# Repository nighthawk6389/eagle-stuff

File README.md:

# eagle-stuff
Stuff I made for PCB in Eagle

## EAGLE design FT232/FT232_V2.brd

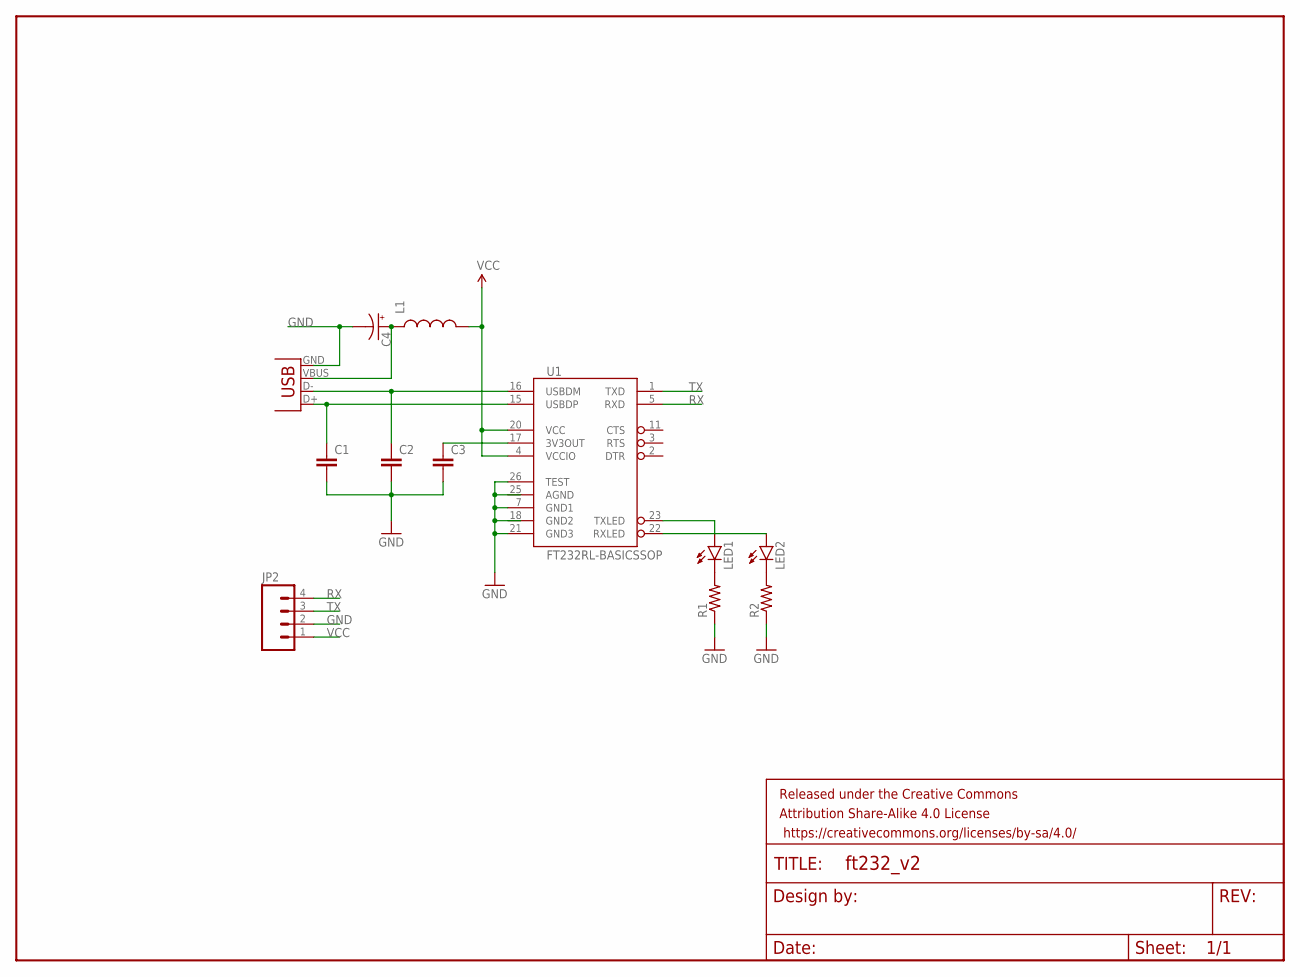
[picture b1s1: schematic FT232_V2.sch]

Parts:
C1, C2, C3: CAP0603-CAP; 0603-CAP
C4: CAP_POL1206; EIA3216
FRAME1: FRAME-LETTER; CREATIVE_COMMONS
JP1: USB-B; USB-B-PTH
JP2: M04PTH; 1X04
L1: INDUCTOR0603; 0603
LED1, LED2: LED0603; LED-0603
R1, R2: RESISTOR0603; 0603-RES
U1: FT232RL-BASICSSOP; SSOP28DB

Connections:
AGND: U1.25 (AGND)
GND: C1.2, C2.2, C3.2, C4.C (-), JP1.GND, JP2.2, R1.1, R2.1, U1.7 (GND1), U1.21 (GND3), U1.26 (TEST)
GND2: U1.18 (GND2)
unnamed: C2.1, JP1.D-, U1.16 (USBDM)
unnamed: C3.1, U1.17 (3V3OUT)
unnamed: C4.A (+), JP1.VBUS, L1.1
unnamed: C1.1, JP1.D+, U1.15 (USBDP)
unnamed: LED1.C, R1.2
unnamed: LED2.C, R2.2
unnamed: LED1.A, U1.23 (TXLED)
unnamed: LED2.A, U1.22 (RXLED)
RX: JP2.4, U1.5 (RXD)
TX: JP2.3, U1.1 (TXD)
VCC: JP2.1, L1.2, U1.4 (VCCIO), U1.20 (VCC)

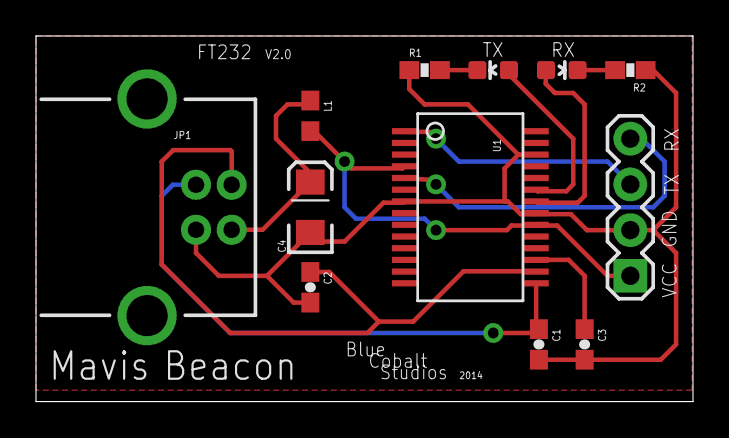
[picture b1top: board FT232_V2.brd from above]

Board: 2 copper layers, 36.5 x 20.3 mm, 13 parts (0 on the bottom side), 12 nets.

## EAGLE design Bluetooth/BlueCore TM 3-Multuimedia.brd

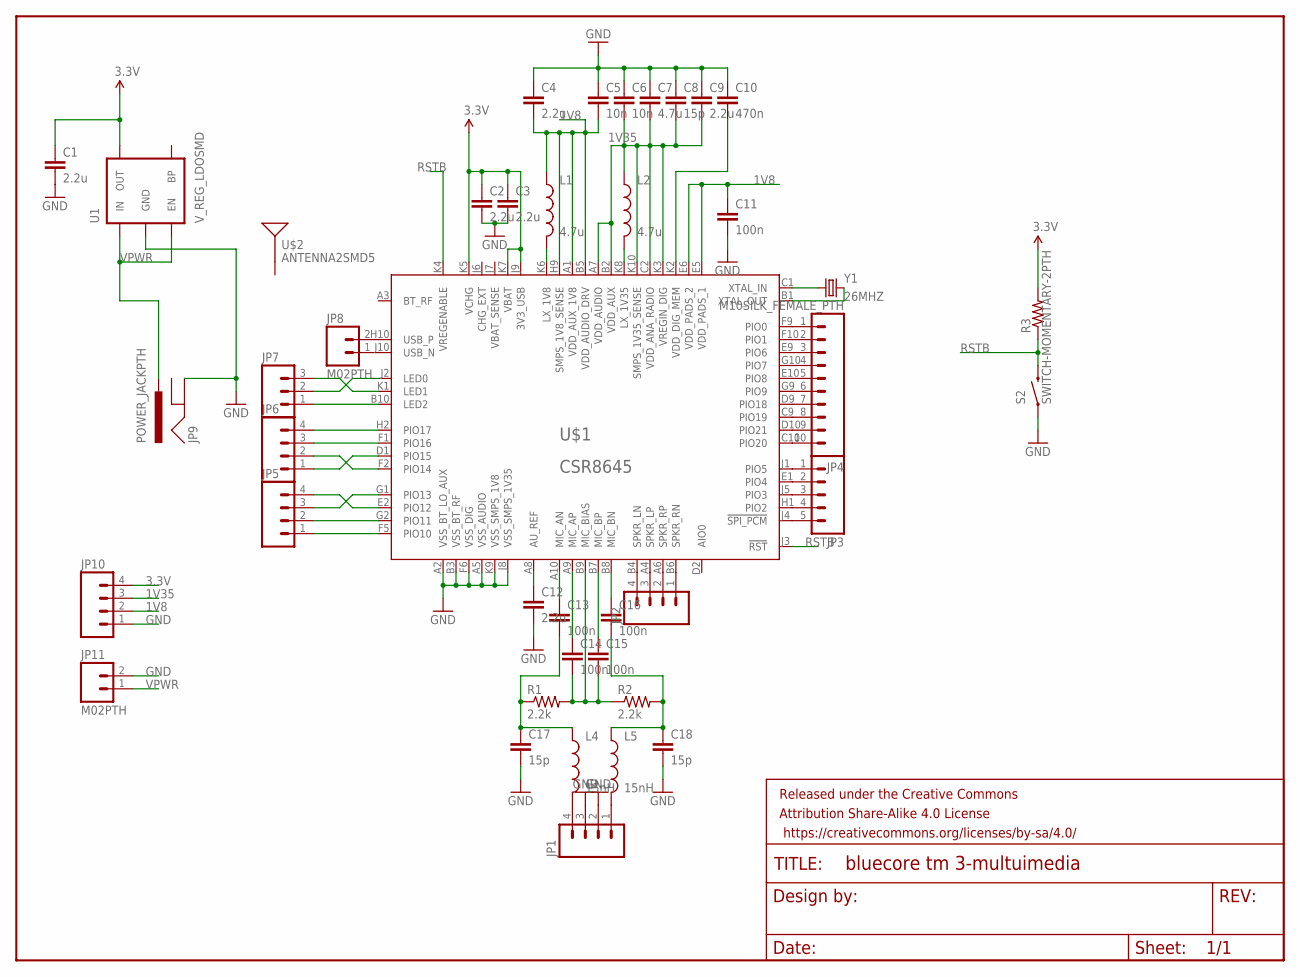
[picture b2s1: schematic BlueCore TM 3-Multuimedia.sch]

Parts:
C1, C2, C3, C4, C9, C12: 2.2u; CAP-PTH-SMALL
C5, C6: 10n; CAP-PTH-SMALL
C7: 4.7u; CAP-PTH-SMALL
C8, C17, C18: 15p; CAP-PTH-SMALL
C10: 470n; CAP-PTH-SMALL
C11, C13, C14, C15, C16: 100n; CAP-PTH-SMALL
FRAME1: FRAME-LETTER; CREATIVE_COMMONS
JP1, JP2, JP5, JP6, JP10: M04PTH; 1X04
JP3: M05PTH; 1X05
JP4: M10SILK_FEMALE_PTH; 1X10
JP7: M03PTH; 1X03
JP8, JP11: M02PTH; 1X02
JP9: POWER_JACKPTH; POWER_JACK_PTH
L1, L2: 4.7u; 0805
L4, L5: 15nH; 0805
R1, R2: 2.2k; 0805
R3: RESISTOR0805-RES; 0805
S2: SWITCH-MOMENTARY-2PTH; TACTILE-PTH
U1: V_REG_LDOSMD; SOT23-5
U$1: CSR8645; VFBGA68
U$2: ANTENNA2SMD5; ANTENNA-CHIP5
Y1: 26MHZ; HC49US

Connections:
1V8: C4.2, C5.2, C11.1, JP10.2, L1.1, U$1.A1 (VDD_AUX_1V8), U$1.B5 (VDD_AUDIO_DRV), U$1.E5 (VDD_PADS_1), U$1.E6 (VDD_PADS_2), U$1.H9 (SMPS_1V8_SENSE)
1V35: C6.2, C7.2, C8.2, C9.2, JP10.3, L2.1, U$1.A7 (VDD_AUDIO), U$1.B2 (VDD_AUX), U$1.C2 (VDD_ANA_RADIO), U$1.K3 (VREGIN_DIG), U$1.K10 (SMPS_1V35_SENSE)
3.3V: C1.1, C2.1, C3.1, JP10.4, R3.2, U1.5 (OUT), U$1.J9 (3V3_USB), U$1.K5 (VCHG), U$1.K7 (VBAT)
GND: C1.2, C2.2, C3.2, C4.1, C5.1, C6.1, C7.1, C8.1, C9.1, C10.1, C11.2, C12.2, C17.2, C18.2, JP1.2, JP1.3, JP9.GND, JP10.1, JP11.2, S2.1, U1.2 (GND), U$1.A2 (VSS_BT_LO_AUX), U$1.A5 (VSS_AUDIO), U$1.B3 (VSS_BT_RF), U$1.F6 (VSS_DIG), U$1.J8 (VSS_SMPS_1V35), U$1.K9 (VSS_SMPS_1V8)
unnamed: JP1.4, L4.2
unnamed: JP4.1, U$1.F9 (PIO0)
unnamed: L1.2, U$1.K6 (LX_1V8)
unnamed: L2.2, U$1.K8 (LX_1V35)
unnamed: U$1.C1 (XTAL_IN), Y1.1
unnamed: C10.2, U$1.K2 (VDD_DIG_MEM)
unnamed: U$1.B1 (XTAL_OUT), Y1.2
unnamed: C12.1, U$1.A8 (AU_REF)
unnamed: JP1.1, L5.2
unnamed: JP2.1, U$1.B6 (SPKR_RN)
unnamed: C13.2, C17.1, L4.1, R1.1
unnamed: JP2.2, U$1.A6 (SPKR_RP)
unnamed: C14.2, C15.2, R1.2, R2.1, U$1.B9 (MIC_BIAS)
unnamed: C13.1, U$1.A10 (MIC_AN)
unnamed: C14.1, U$1.A9 (MIC_AP)
unnamed: C15.1, U$1.B7 (MIC_BP)
unnamed: C16.1, U$1.B8 (MIC_BN)
unnamed: C16.2, C18.1, L5.1, R2.2
unnamed: JP2.3, U$1.A4 (SPKR_LP)
unnamed: JP2.4, U$1.B4 (SPKR_LN)
unnamed: JP4.2, U$1.F10 (PIO1)
unnamed: JP4.3, U$1.E9 (PIO6)
unnamed: JP4.4, U$1.G10 (PIO7)
unnamed: JP4.5, U$1.E10 (PIO8)
unnamed: JP4.6, U$1.G9 (PIO9)
unnamed: JP4.7, U$1.D9 (PIO18)
unnamed: JP4.8, U$1.C9 (PIO19)
unnamed: JP4.9, U$1.D10 (PIO21)
unnamed: JP4.10, U$1.C10 (PIO20)
unnamed: JP3.1, U$1.J1 (PIO5)
unnamed: JP3.2, U$1.E1 (PIO4)
unnamed: JP3.3, U$1.J5 (PIO3)
unnamed: JP3.4, U$1.H1 (PIO2)
unnamed: JP3.5, U$1.J4 (!SPI_PCM)
unnamed: JP5.1, U$1.F5 (PIO10)
unnamed: JP5.2, U$1.G2 (PIO11)
unnamed: JP5.4, U$1.E2 (PIO12)
unnamed: JP5.3, U$1.G1 (PIO13)
unnamed: JP6.1, U$1.D1 (PIO15)
unnamed: JP6.2, U$1.F2 (PIO14)
unnamed: JP6.3, U$1.F1 (PIO16)
unnamed: JP6.4, U$1.H2 (PIO17)
unnamed: JP7.1, U$1.B10 (LED2)
unnamed: JP7.3, U$1.K1 (LED1)
unnamed: JP7.2, U$1.J2 (LED0)
unnamed: JP8.1, U$1.J10 (USB_N)
unnamed: JP8.2, U$1.H10 (USB_P)
RSTB: R3.1, S2.3 (2), U$1.J3 (!RST), U$1.K4 (VREGENABLE)
VPWR: JP9.PWR, JP11.1, U1.1 (IN), U1.3 (EN)

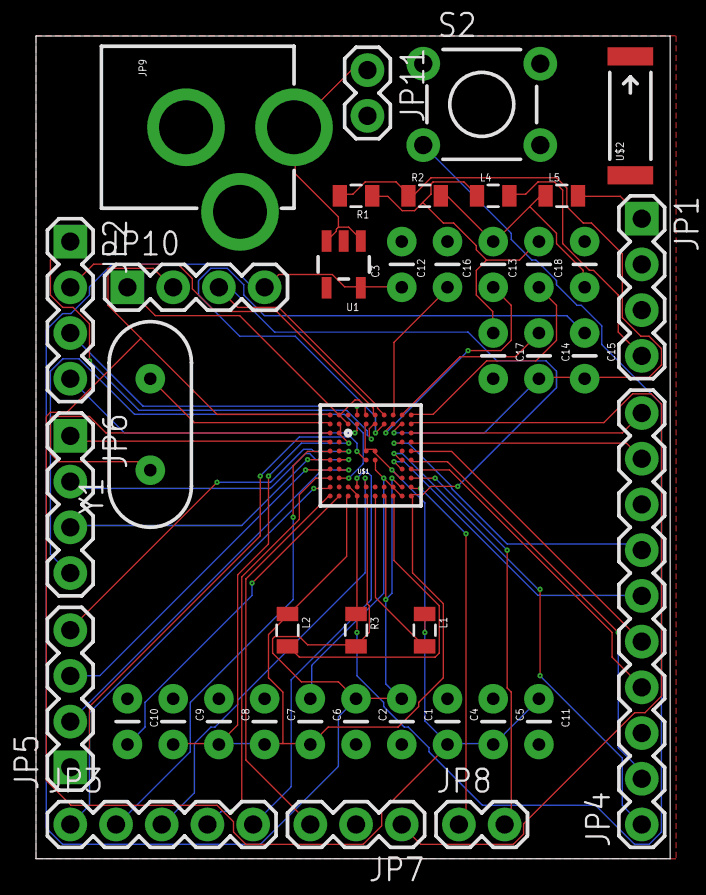
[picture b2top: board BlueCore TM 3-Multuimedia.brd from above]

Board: 2 copper layers, 35.2 x 45.7 mm, 42 parts (0 on the bottom side), 53 nets.

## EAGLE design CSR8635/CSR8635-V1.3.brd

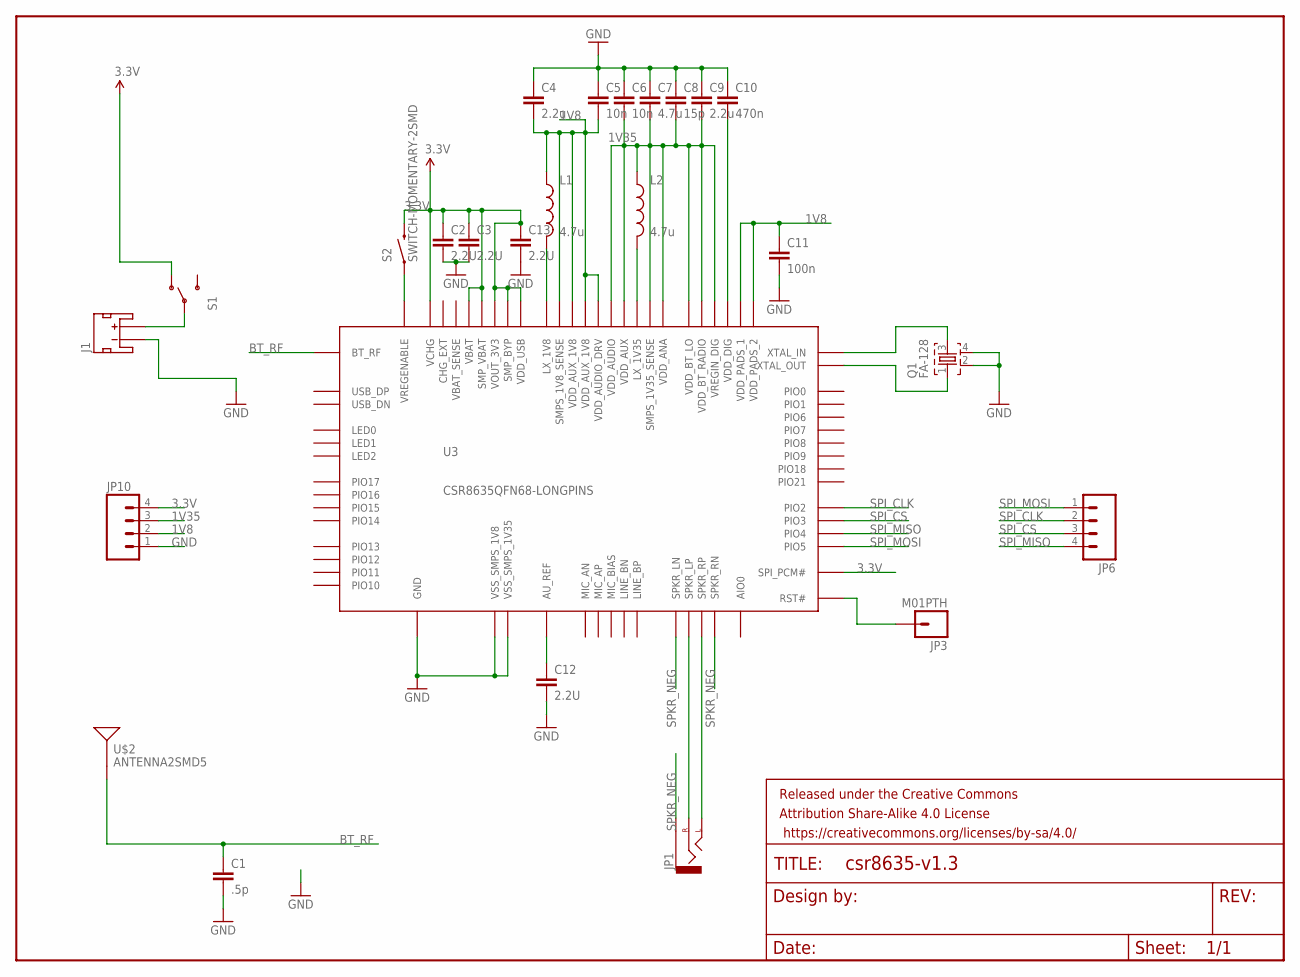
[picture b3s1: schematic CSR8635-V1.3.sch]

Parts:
C1: .5p; 0603-CAP
C2, C3, C12, C13: 2.2U; 0603-CAP
C4, C9: 2.2u; 0603-CAP
C5, C6: 10n; 0603-CAP
C7: 4.7u; 0603-CAP
C8: 15p; 0603-CAP
C10: 470n; 0603-CAP
C11: 100n; 0603-CAP
FRAME1: FRAME-LETTER; CREATIVE_COMMONS
J1: JST_2MM_MALE; JST-2-SMD
JP1: AUDIO-JACKSMD2; AUDIO-JACK-3.5MM-SMD
JP3: M01PTH; 1X01
JP6, JP10: M04PTH; 1X04
L1, L2: 4.7u; 0805
Q1: FA-128
S1: SWITCH-SPDTPTH; SWITCH-SPDT
S2: SWITCH-MOMENTARY-2SMD; TACTILE-SWITCH-SMD
U3: CSR8635QFN68-LONGPINS; QFN68
U$2: ANTENNA2SMD5; ANTENNA-CHIP5

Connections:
1V8: C4.2, C5.2, C11.1, JP10.2, L1.1, U3.8 (VDD_AUDIO_DRV), U3.15 (VDD_AUX_1V8), U3.16 (VDD_AUX_1V8), U3.33 (VDD_PADS_1), U3.53 (SMPS_1V8_SENSE), U3.63 (VDD_PADS_2)
1V35: C6.2, C7.2, C8.2, C9.2, JP10.3, L2.1, U3.3 (VDD_AUDIO), U3.11 (VDD_BT_RADIO), U3.13 (VDD_BT_LO), U3.14 (VDD_AUX), U3.17 (VDD_ANA), U3.39 (VREGIN_DIG), U3.52 (SMPS_1V35_SENSE)
3.3V: C2.1, C3.1, C13.1, JP10.4, S1.1 (O), S2.3 (2), U3.29 (SPI_PCM#), U3.41 (VOUT_3V3), U3.42 (VCHG), U3.45 (VBAT), U3.48 (SMP_VBAT), U3.49 (SMP_BYP), U3.54 (VDD_USB)
!SPI_PCM: JP3.1, U3.35 (RST#)
BT_RF: C1.1, U3.12 (BT_RF), U$2.FEED
GND: C1.2, C2.2, C3.2, C4.1, C5.1, C6.1, C7.1, C8.1, C9.1, C10.1, C11.2, C12.2, C13.2, J1.1 (-), JP10.1, Q1.2, Q1.4, U3.46 (VSS_SMPS_1V8), U3.51 (VSS_SMPS_1V35), U3.CNTR (GND), U3.CNTR1 (GND), U3.CNTR2 (GND), U3.CNTR3 (GND)
unnamed: J1.2 (+), S1.2
unnamed: JP1.RING (RIGHT), U3.10 (SPKR_LP)
unnamed: L1.2, U3.47 (LX_1V8)
unnamed: Q1.3, U3.19 (XTAL_IN)
unnamed: L2.2, U3.50 (LX_1V35)
unnamed: C10.2, U3.38 (VDD_DIG)
unnamed: Q1.1, U3.18 (XTAL_OUT)
unnamed: JP1.TIP (LEFT), U3.7 (SPKR_RP)
unnamed: C12.1, U3.1 (AU_REF)
unnamed: S2.1, U3.40 (VREGENABLE)
SPI_CLK: JP6.2, U3.30 (PIO2)
SPI_CS: JP6.3, U3.28 (PIO3)
SPI_MISO: JP6.4, U3.24 (PIO4)
SPI_MOSI: JP6.1, U3.34 (PIO5)
SPKR_NEG: JP1.SLEEVE, U3.6 (SPKR_RN), U3.9 (SPKR_LN)

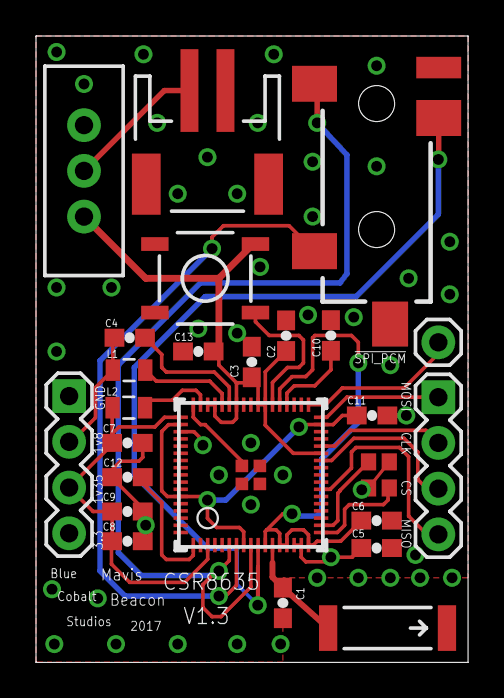
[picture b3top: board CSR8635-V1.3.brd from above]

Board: 4 copper layers, 24.0 x 34.8 mm, 26 parts (0 on the bottom side), 21 nets.

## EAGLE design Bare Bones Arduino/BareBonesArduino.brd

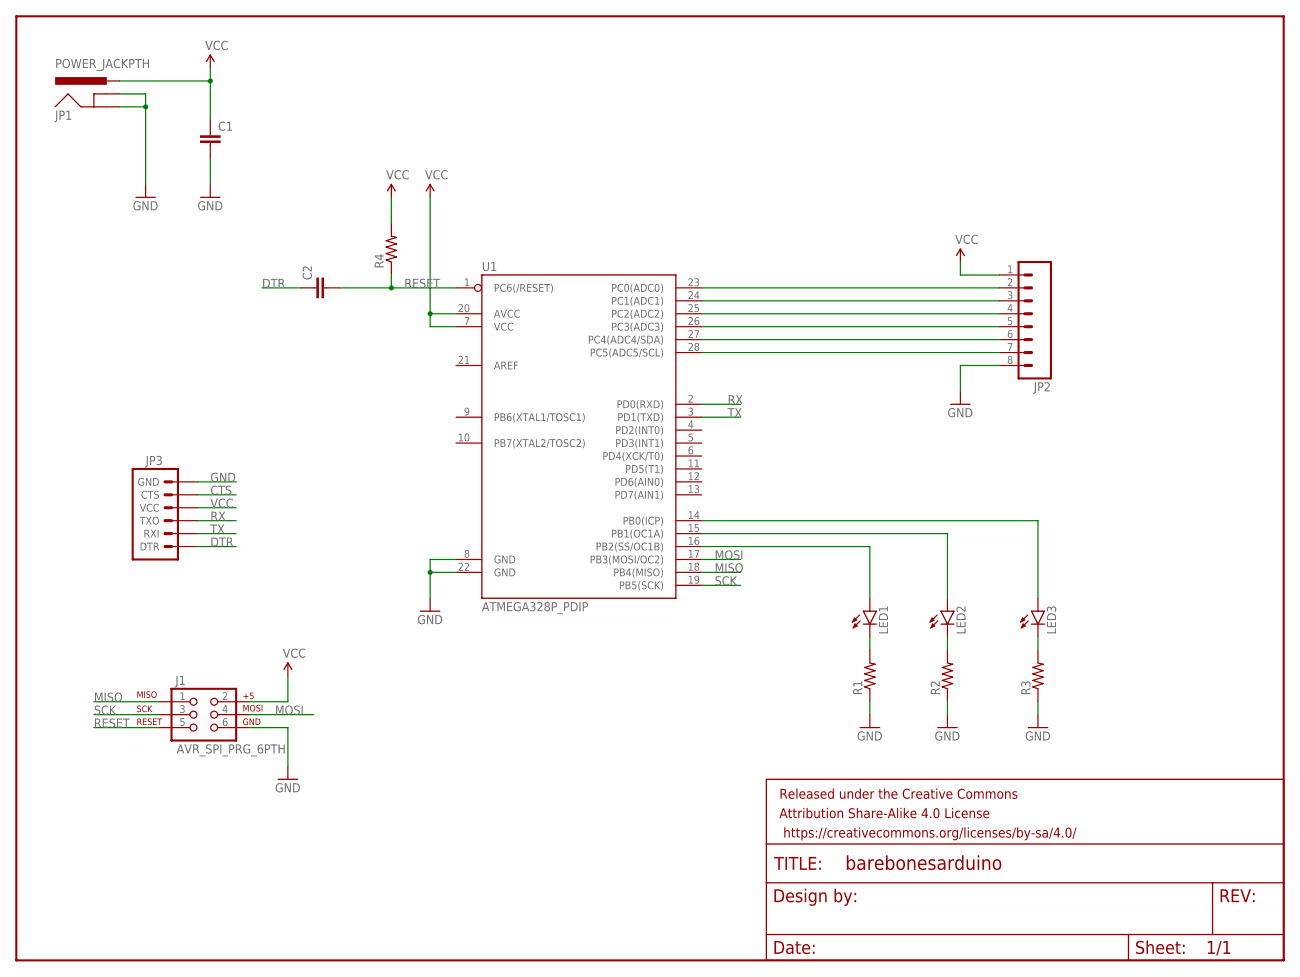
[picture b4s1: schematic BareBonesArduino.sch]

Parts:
C1, C2: CAPPTH; CAP-PTH-SMALL
FRAME1: FRAME-LETTER; CREATIVE_COMMONS
J1: AVR_SPI_PRG_6PTH; 2X3
JP1: POWER_JACKPTH; POWER_JACK_PTH
JP2: M08; 1X08_ROUND
JP3: ARDUINO_SERIAL_PROGRAMPTH; 1X06
LED1, LED2, LED3: LED5MM
R1, R2, R3, R4: RESISTORPTH-1/4W; AXIAL-0.4
U1: ATMEGA328P_PDIP; DIL28-3

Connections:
CTS: JP3.5 (CTS)
DTR: C2.1, JP3.1 (DTR)
GND: C1.2, J1.6, JP1.GND, JP1.GNDBREAK, JP2.8, JP3.6 (GND), R1.P$1 (1), R2.P$1 (1), R3.P$1 (1), U1.8 (GND), U1.22 (GND)
MISO: J1.1, U1.18 (PB4(MISO))
MOSI: J1.4, U1.17 (PB3(MOSI/OC2))
unnamed: LED3.K (C), R3.P$2 (2)
unnamed: LED2.K (C), R2.P$2 (2)
unnamed: LED1.K (C), R1.P$2 (2)
unnamed: LED1.A, U1.16 (PB2(SS/OC1B))
unnamed: LED2.A, U1.15 (PB1(OC1A))
unnamed: LED3.A, U1.14 (PB0(ICP))
unnamed: JP2.7, U1.28 (PC5(ADC5/SCL))
unnamed: JP2.6, U1.27 (PC4(ADC4/SDA))
unnamed: JP2.5, U1.26 (PC3(ADC3))
unnamed: JP2.4, U1.25 (PC2(ADC2))
unnamed: JP2.3, U1.24 (PC1(ADC1))
unnamed: JP2.2, U1.23 (PC0(ADC0))
RESET: C2.2, J1.5, R4.P$1 (1), U1.1 (PC6(/RESET))
RX: JP3.3 (TXO), U1.2 (PD0(RXD))
SCK: J1.3, U1.19 (PB5(SCK))
TX: JP3.2 (RXI), U1.3 (PD1(TXD))
VCC: C1.1, J1.2, JP1.PWR, JP2.1, JP3.4 (VCC), R4.P$2 (2), U1.7 (VCC), U1.20 (AVCC)

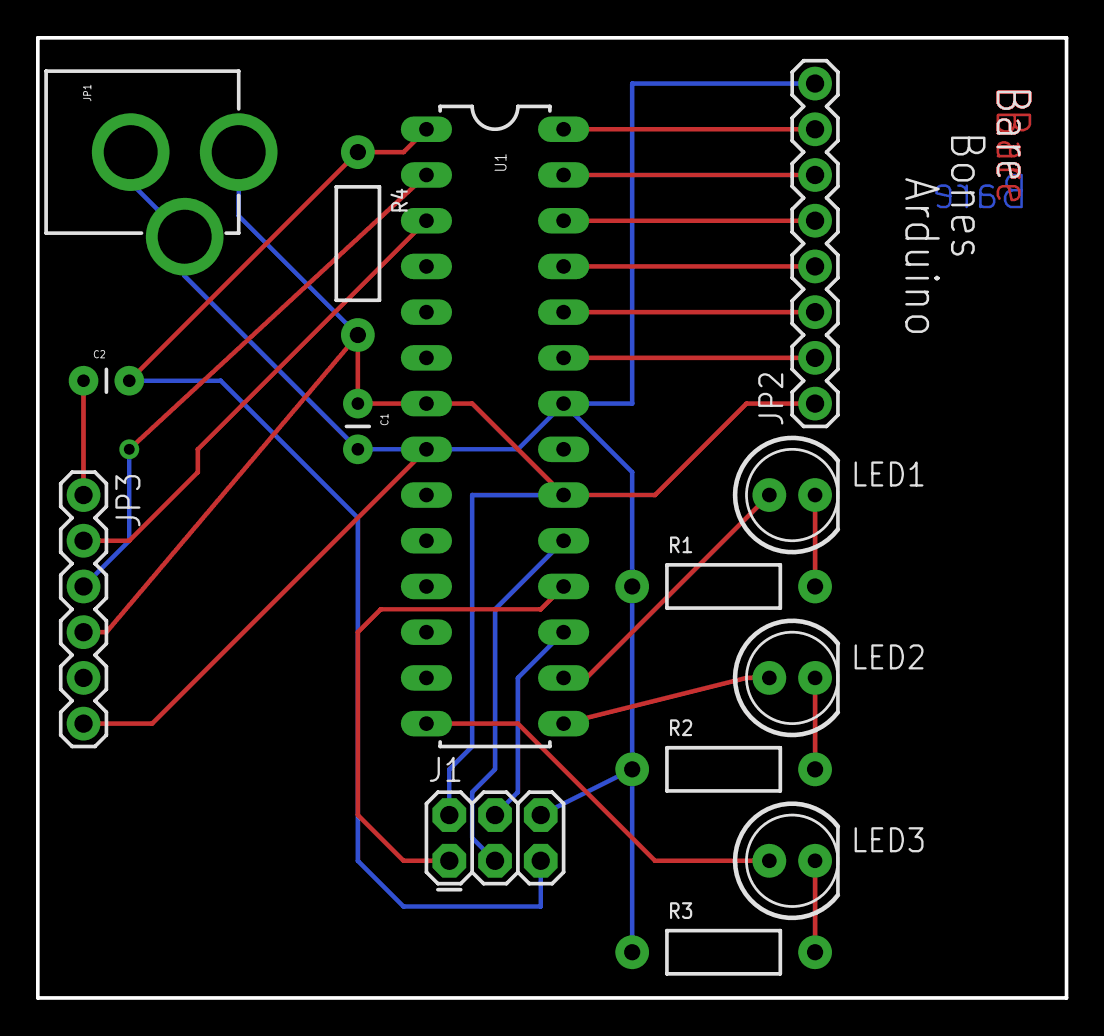
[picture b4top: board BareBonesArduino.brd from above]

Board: 2 copper layers, 57.1 x 53.3 mm, 15 parts (0 on the bottom side), 21 nets.

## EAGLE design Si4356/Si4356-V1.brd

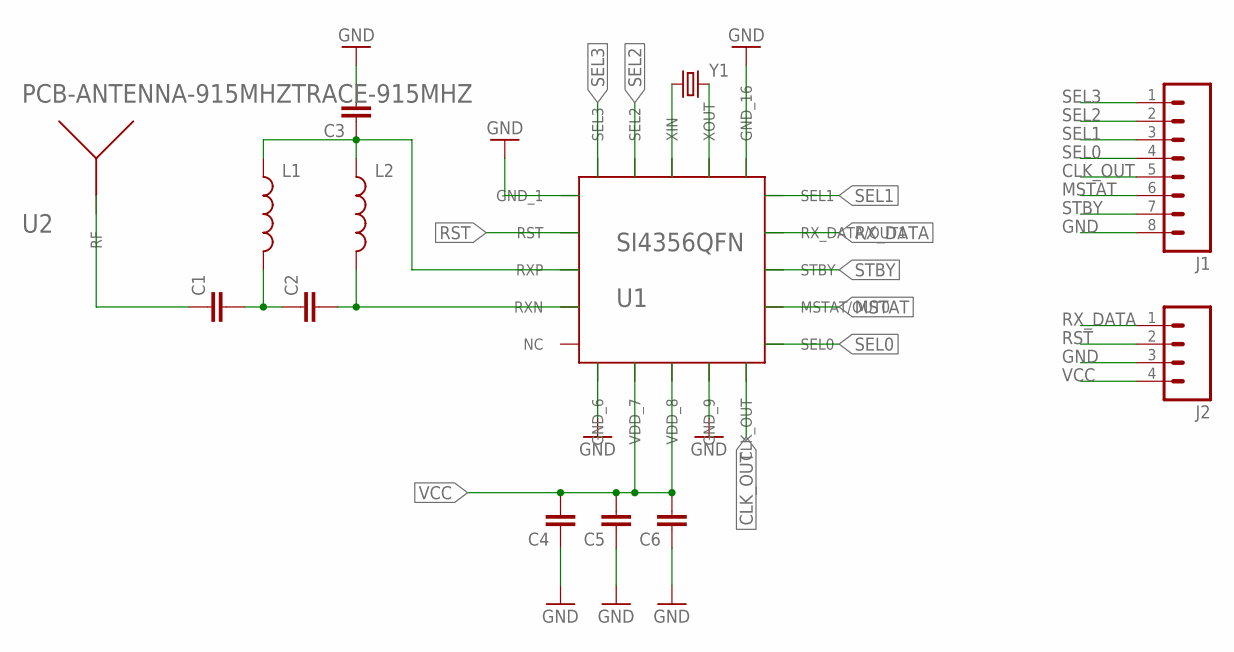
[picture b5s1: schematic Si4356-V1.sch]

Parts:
C1, C2, C3, C4, C5, C6: CAP0603-CAP; 0603-CAP
J1: M08; 1X08_ROUND
J2: M04PTH; 1X04
L1, L2: INDUCTOR0805; 0805
U1: SI4356QFN; QFN20-3X3MM
U2: PCB-ANTENNA-915MHZTRACE-915MHZ; PCB-ANTENNA-915MHZ-16.8MM
Y1: CRYSTALHC49US; HC49US

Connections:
CLK_OUT: J1.5, U1.10 (CLK_OUT)
GND: C3.2, C4.1, C5.1, C6.1, J1.8, J2.3, U1.1 (GND_1), U1.6 (GND_6), U1.9 (GND_9), U1.16 (GND_16)
MSTAT: J1.6, U1.12 (MSTAT/OUT0)
unnamed: C1.2, C2.1, L1.2
unnamed: U1.18 (XIN), Y1.1
unnamed: U1.17 (XOUT), Y1.2
unnamed: C1.1, U2.1
RST: J2.2, U1.2 (RST)
RXN: C2.2, L2.2, U1.4 (RXN)
RXP: C3.1, L1.1, L2.1, U1.3 (RXP)
RX_DATA: J2.1, U1.14 (RX_DATA/OUT1)
SEL0: J1.4, U1.11 (SEL0)
SEL1: J1.3, U1.15 (SEL1)
SEL2: J1.2, U1.19 (SEL2)
SEL3: J1.1, U1.20 (SEL3)
STBY: J1.7, U1.13 (STBY)
VCC: C4.2, C5.2, C6.2, J2.4, U1.7 (VDD_7), U1.8 (VDD_8)

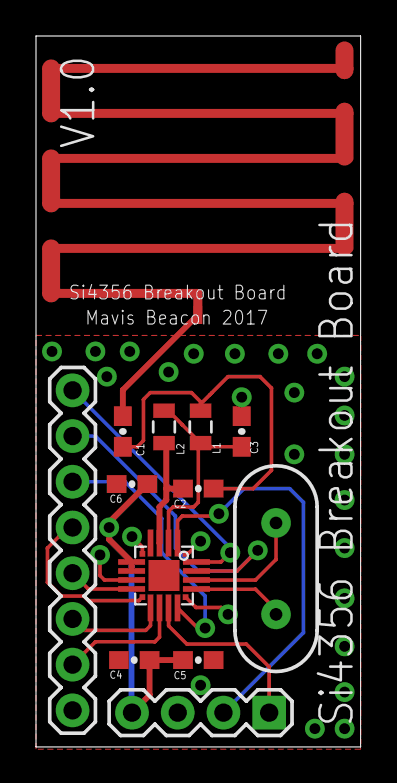
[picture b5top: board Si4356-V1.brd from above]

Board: 2 copper layers, 18.0 x 39.5 mm, 13 parts (0 on the bottom side), 17 nets.

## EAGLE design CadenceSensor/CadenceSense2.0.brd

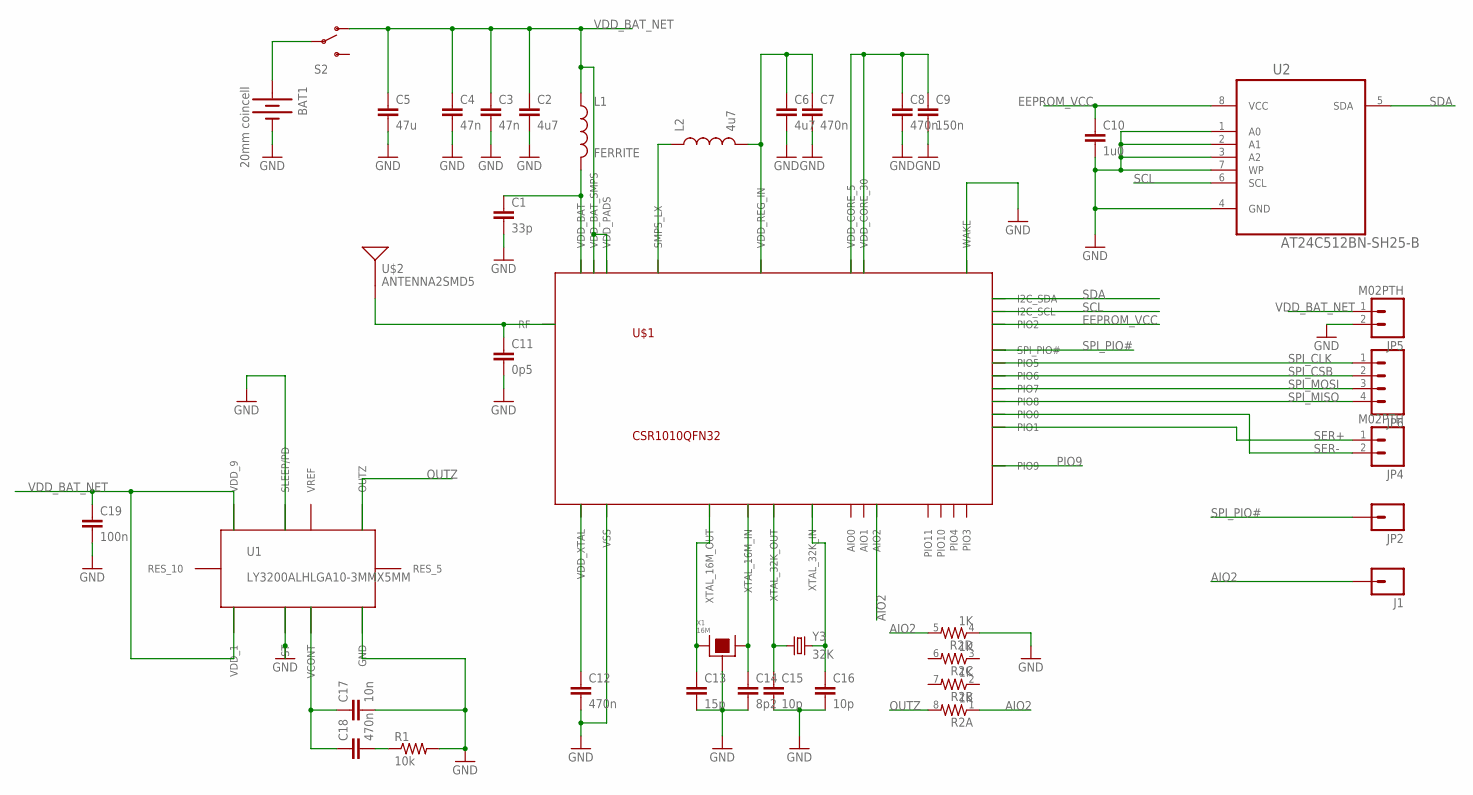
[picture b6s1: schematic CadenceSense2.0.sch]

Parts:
BAT1: 20mm coincell; BATTCON_20MM_4LEGS
C1: 33p; 0603-CAP
C2, C6: 4u7; 0603-CAP
C3, C4: 47n; 0603-CAP
C5: 47u; 0603-CAP
C7, C8, C12, C18: 470n; 0603-CAP
C9: 150n; 0603-CAP
C10: 1u0; 0603-CAP
C11: 0p5; 0603-CAP
C13: 15p; 0603-CAP
C14: 8p2; 0603-CAP
C15, C16: 10p; 0603-CAP
C17: 10n; 0603-CAP
C19: 100n; 0603-CAP
J1: M01PTH; 1X01
JP2: M01PTH; 1X01
JP4, JP5: M02PTH; 1X02
JP6: M04PTH; 1X04
L1: FERRITE; 0805
L2: 4u7; 0805
R1: 10k; 0603-RES
R2: 1K; 0603-ARV
S2: SWITCH-SPDTSMD; AYZ0202
U1: LY3200ALHLGA10-3MMX5MM; LGA10
U2: AT24C512BN-SH25-B; SOIC127P600X175-8N
U$1: CSR1010QFN32; QFN-32
U$2: ANTENNA2SMD5; ANTENNA-CHIP5
X1: 16M; TSX-3225
Y3: 32K; CRYSTAL-32KHZ-SMD_EPSON_MC146

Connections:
AIO2: J1.1, R2.1, R2.5 (2), U$1.11 (AIO2)
EEPROM_VCC: C10.1, U2.8 (VCC), U$1.27 (PIO2)
GND: BAT1.2 (-), C1.2, C2.2, C3.2, C4.2, C5.2, C6.2, C7.2, C8.2, C9.2, C10.2, C11.2, C12.2, C13.2, C14.2, C15.2, C16.2, C17.2, C19.2, JP5.2, R1.2, R2.4 (1), U1.2 (ST), U1.4 (GND), U1.8 (SLEEP/PD), U2.1 (A0), U2.2 (A1), U2.3 (A2), U2.4 (GND), U2.7 (WP), U$1.4 (WAKE), U$1.EP (VSS), X1.2, X1.4
unnamed: BAT1.1 (+), S2.2
unnamed: C6.1, C7.1, L2.2, U$1.6 (VDD_REG_IN)
unnamed: C1.1, L1.2, U$1.1 (VDD_BAT)
unnamed: C11.1, U$1.7 (RF), U$2.FEED
unnamed: C16.1, U$1.3 (XTAL_32K_IN), Y3.P$1 (2)
unnamed: L2.1, U$1.31 (SMPS_LX)
unnamed: C8.1, C9.1, U$1.5 (VDD_CORE_5), U$1.30 (VDD_CORE_30)
unnamed: C15.1, U$1.2 (XTAL_32K_OUT), Y3.P$2 (1)
unnamed: C14.1, U$1.10 (XTAL_16M_IN), X1.3
unnamed: C13.1, U$1.9 (XTAL_16M_OUT), X1.1
unnamed: C12.1, U$1.8 (VDD_XTAL)
unnamed: C17.1, C18.1, U1.3 (VCONT)
unnamed: C18.2, R1.1
OUTZ: R2.8 (2), U1.6 (OUTZ)
PIO9: U$1.23 (PIO9)
SCL: U2.6 (SCL), U$1.28 (I2C_SCL)
SDA: U2.5 (SDA), U$1.29 (I2C_SDA)
SER+: JP4.1, U$1.15 (PIO1)
SER-: JP4.2, U$1.14 (PIO0)
SPI_CLK: JP6.1, U$1.18 (PIO5)
SPI_CSB: JP6.2, U$1.19 (PIO6)
SPI_MISO: JP6.4, U$1.22 (PIO8)
SPI_MOSI: JP6.3, U$1.20 (PIO7)
SPI_PIO#: JP2.1, U$1.26 (SPI_PIO#)
VDD_BAT_NET: C2.1, C3.1, C4.1, C5.1, C19.1, JP5.1, L1.1, S2.1 (O), U1.1 (VDD_1), U1.9 (VDD_9), U$1.21 (VDD_PADS), U$1.32 (VDD_BAT_SMPS)

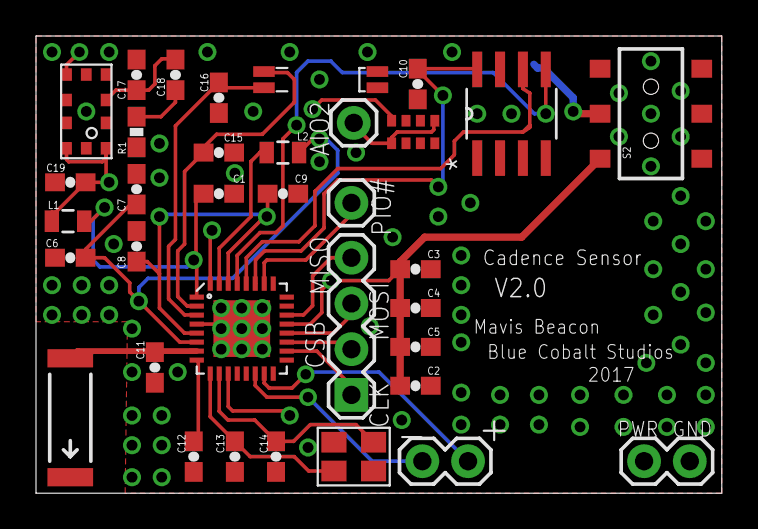
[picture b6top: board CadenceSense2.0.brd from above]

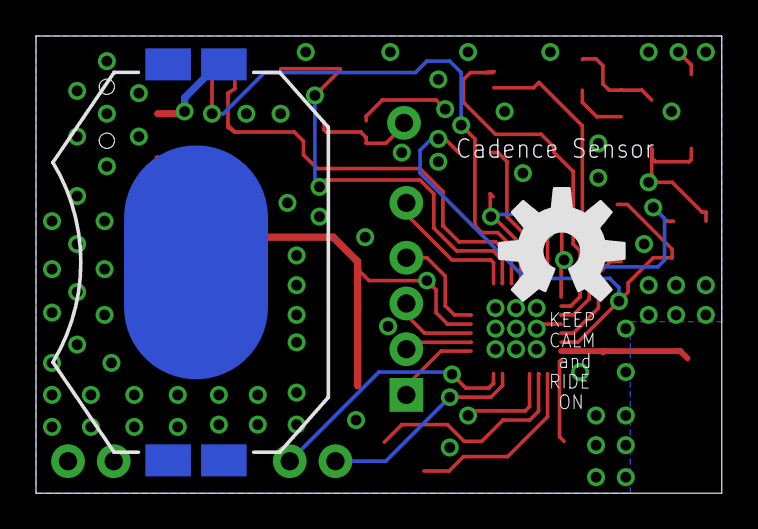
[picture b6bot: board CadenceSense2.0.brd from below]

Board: 4 copper layers, 38.1 x 25.4 mm, 37 parts (2 on the bottom side), 27 nets.

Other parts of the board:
U$3: OSHW-LOGO-L

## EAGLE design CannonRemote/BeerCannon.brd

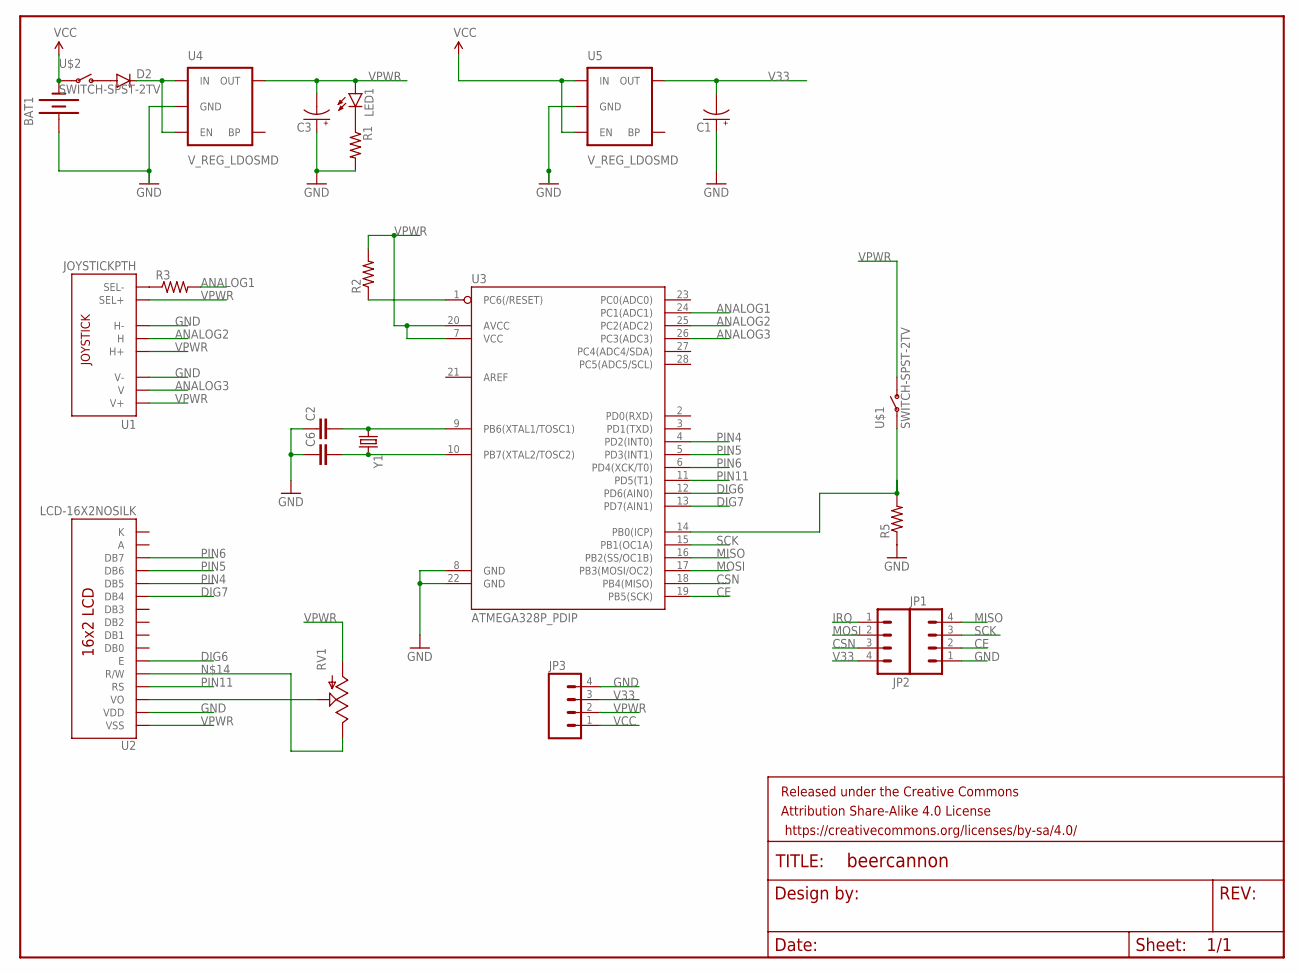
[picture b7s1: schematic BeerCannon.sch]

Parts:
BAT1: BATTERY9V; BATTCON_9V
C1, C3: CAP_POL1206; EIA3216
C2, C6: CAP1206; 1206
D2: DIODESMA; SMA-DIODE
FRAME1: FRAME-LETTER; CREATIVE_COMMONS
JP1, JP2, JP3: M04PTH; 1X04
LED1: LED1206; LED-1206
R1, R2, R3, R5: RESISTOR1206; 1206
RV1: POT; ALPS_POT
U1: JOYSTICKPTH; JOYSTICK
U2: LCD-16X2NOSILK; LCD-16X2_NOSILK
U3: ATMEGA328P_PDIP; DIL28-3
U4, U5: V_REG_LDOSMD; SOT23-5
U$1, U$2: SWITCH-SPST-2TV; SWITCH-SPST-VERTICAL
Y1: CRYSTALSMD; HC49UP

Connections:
A: U2.15 (A)
ANALOG1: R3.2, U3.24 (PC1(ADC1))
ANALOG2: U1.H2 (H), U3.25 (PC2(ADC2))
ANALOG3: U1.V2 (V), U3.26 (PC3(ADC3))
CE: JP1.2, U3.19 (PB5(SCK))
CSN: JP2.3, U3.18 (PB4(MISO))
DIG6: U2.6 (E), U3.12 (PD6(AIN0))
DIG7: U2.11 (DB4), U3.13 (PD7(AIN1))
GND: BAT1.+, C1.A (+), C2.1, C3.A (+), C6.1, JP1.1, JP3.4, R1.2, R5.1, U1.H3 (H-), U1.V3 (V-), U2.2 (VDD), U3.8 (GND), U3.22 (GND), U4.2 (GND), U5.2 (GND)
IRQ: JP2.1
K: U2.16 (K)
MISO: JP1.4, U3.16 (PB2(SS/OC1B))
MOSI: JP2.2, U3.17 (PB3(MOSI/OC2))
unnamed: LED1.C, R1.1
unnamed: D2.A, U$2.1 (O)
unnamed: R3.1, U1.B2A (SEL-)
unnamed: R2.1, U3.1 (PC6(/RESET))
unnamed: C2.2, U3.9 (PB6(XTAL1/TOSC1)), Y1.1
unnamed: C6.2, U3.10 (PB7(XTAL2/TOSC2)), Y1.2
unnamed: D2.C, U4.1 (IN), U4.3 (EN)
unnamed: RV1.P$2 (S), U2.3 (VO)
unnamed: R5.2, U3.14 (PB0(ICP)), U$1.2
unnamed: RV1.P$1 (E), U2.5 (R/W)
PIN4: U2.12 (DB5), U3.4 (PD2(INT0))
PIN5: U2.13 (DB6), U3.5 (PD3(INT1))
PIN6: U2.14 (DB7), U3.6 (PD4(XCK/T0))
PIN11: U2.4 (RS), U3.11 (PD5(T1))
SCK: JP1.3, U3.15 (PB1(OC1A))
V33: C1.C (-), JP2.4, JP3.3, U5.5 (OUT)
VCC: BAT1.-, JP3.1, U5.1 (IN), U5.3 (EN), U$2.2
VPWR: C3.C (-), JP3.2, LED1.A, R2.2, RV1.P$3 (A), U1.B1A (SEL+), U1.H1 (H+), U1.V1 (V+), U2.1 (VSS), U3.7 (VCC), U3.20 (AVCC), U4.5 (OUT), U$1.1 (O)

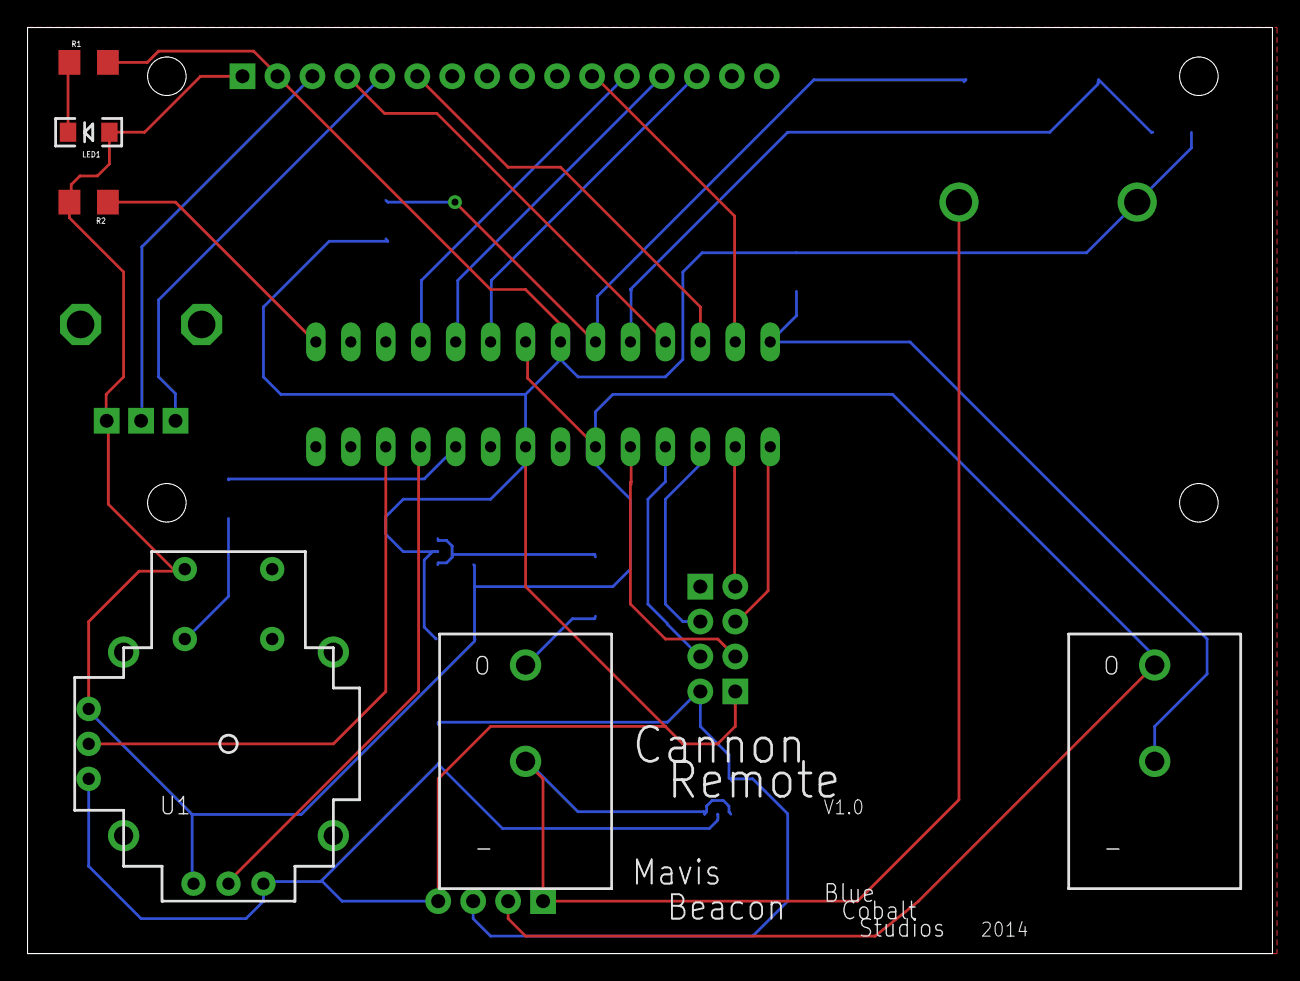
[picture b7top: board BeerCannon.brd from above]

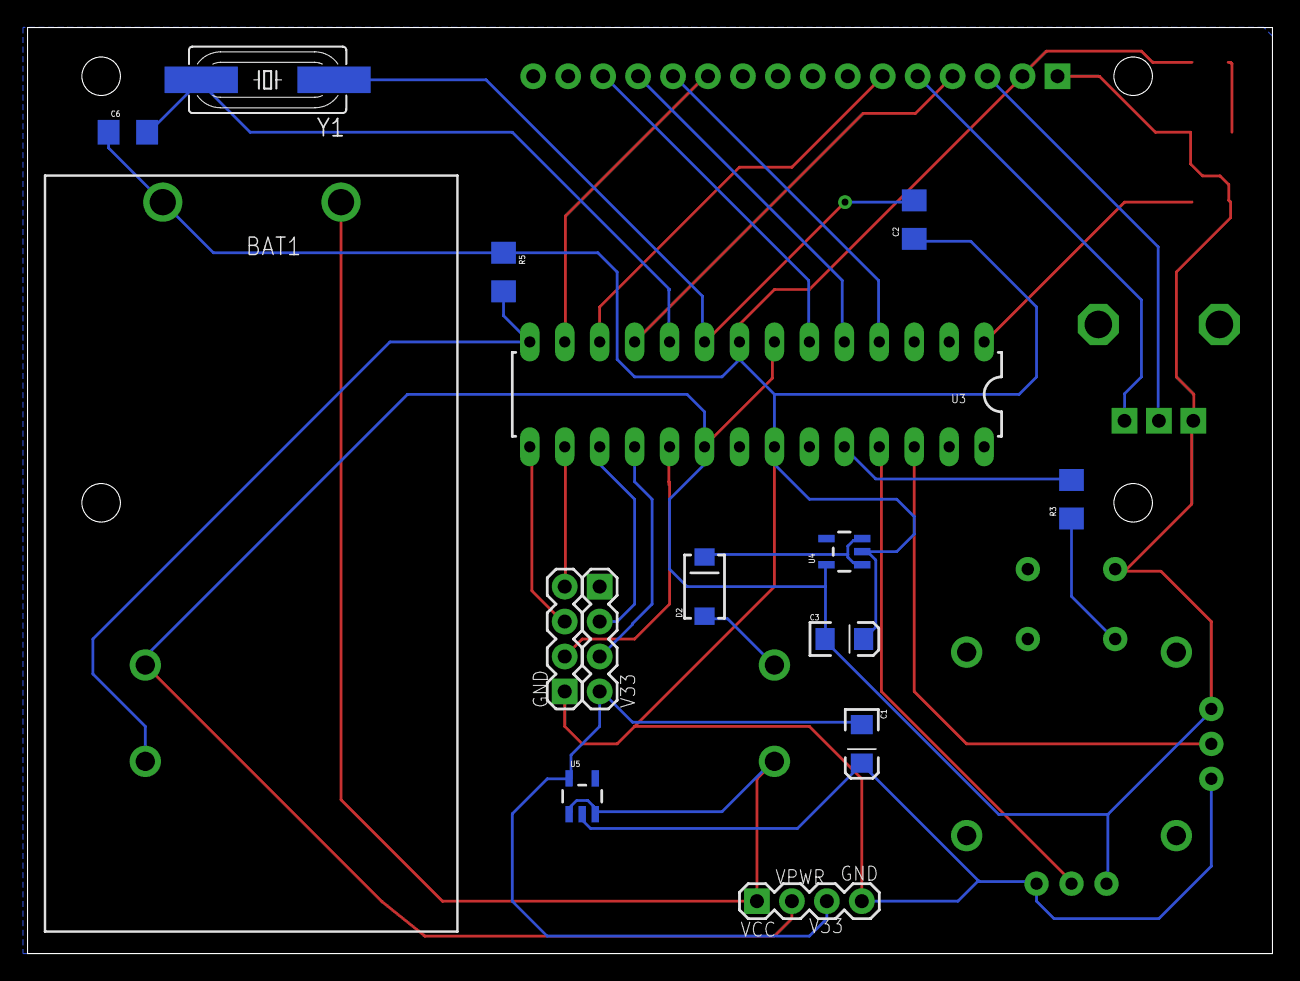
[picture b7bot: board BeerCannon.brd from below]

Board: 2 copper layers, 90.5 x 67.3 mm, 24 parts (16 on the bottom side), 28 nets.

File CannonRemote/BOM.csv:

Part,Value,Device,Package,Description,,
BAT1,,BATTERY9V,BATTCON_9V,Battery Holders,,
C1,,CAP_POL1206,EIA3216,Capacitor Polarized,2.2uf,
C2,,CAP1206,1206,Capacitor,22pf,
C3,,CAP_POL1206,EIA3216,Capacitor Polarized,2.2uf,299-3690-1-nd
C6,,CAP1206,1206,Capacitor,22pf,399-11987-1-nd
D2,,DIODESMA,SMA-DIODE,Diode,,s1afsct-nd
,,,,,,
JP1,,M04PTH,1X04,Header 4,,
JP2,,M04PTH,1X04,Header 4,,
JP3,,M04PTH,1X04,Header 4,,
LED1,,LED1206,LED-1206,LEDs,,
R1,,RESISTOR1206,1206,Resistor,180,
R2,,RESISTOR1206,1206,Resistor,1k,
R3,,RESISTOR1206,1206,Resistor,1k,need to be pulldown
R5,,RESISTOR1206,1206,Resistor,10k,
RV1,,POT,ALPS_POT,,,
U$1,SWITCH-SPST-2TV,SWITCH-SPST-2TV,SWITCH-SPST-VERTICAL,,,
U$2,SWITCH-SPST-2TV,SWITCH-SPST-2TV,SWITCH-SPST-VERTICAL,,,
U1,JOYSTICKPTH,JOYSTICKPTH,JOYSTICK,Thumb Joystick,,
U2,LCD-16X2NOSILK,LCD-16X2NOSILK,LCD-16X2_NOSILK,Standard text-only 16x2 parallel input LCD,,
U3,ATMEGA328P_PDIP,ATMEGA328P_PDIP,DIL28-3,uC used in the Arduino,,
U4,V_REG_LDOSMD,V_REG_LDOSMD,SOT23-5,Voltage Regulator LDO,5V,
U5,V_REG_LDOSMD,V_REG_LDOSMD,SOT23-5,Voltage Regulator LDO,3.3V,
Y1,,CRYSTALSMD,HC49UP,Various standard crystals. Proven footprints.,,

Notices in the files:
parts and their libraries:
SparkFun-Capacitors: Licensing: Creative Commons ShareAlike 4.0 International - https://creativecommons.org/licenses/by-sa/4.0
SparkFun-Aesthetics: Released under the Creative Commons Attribution Share-Alike 4.0 License
SparkFun-Aesthetics: https://creativecommons.org/licenses/by-sa/4.0
